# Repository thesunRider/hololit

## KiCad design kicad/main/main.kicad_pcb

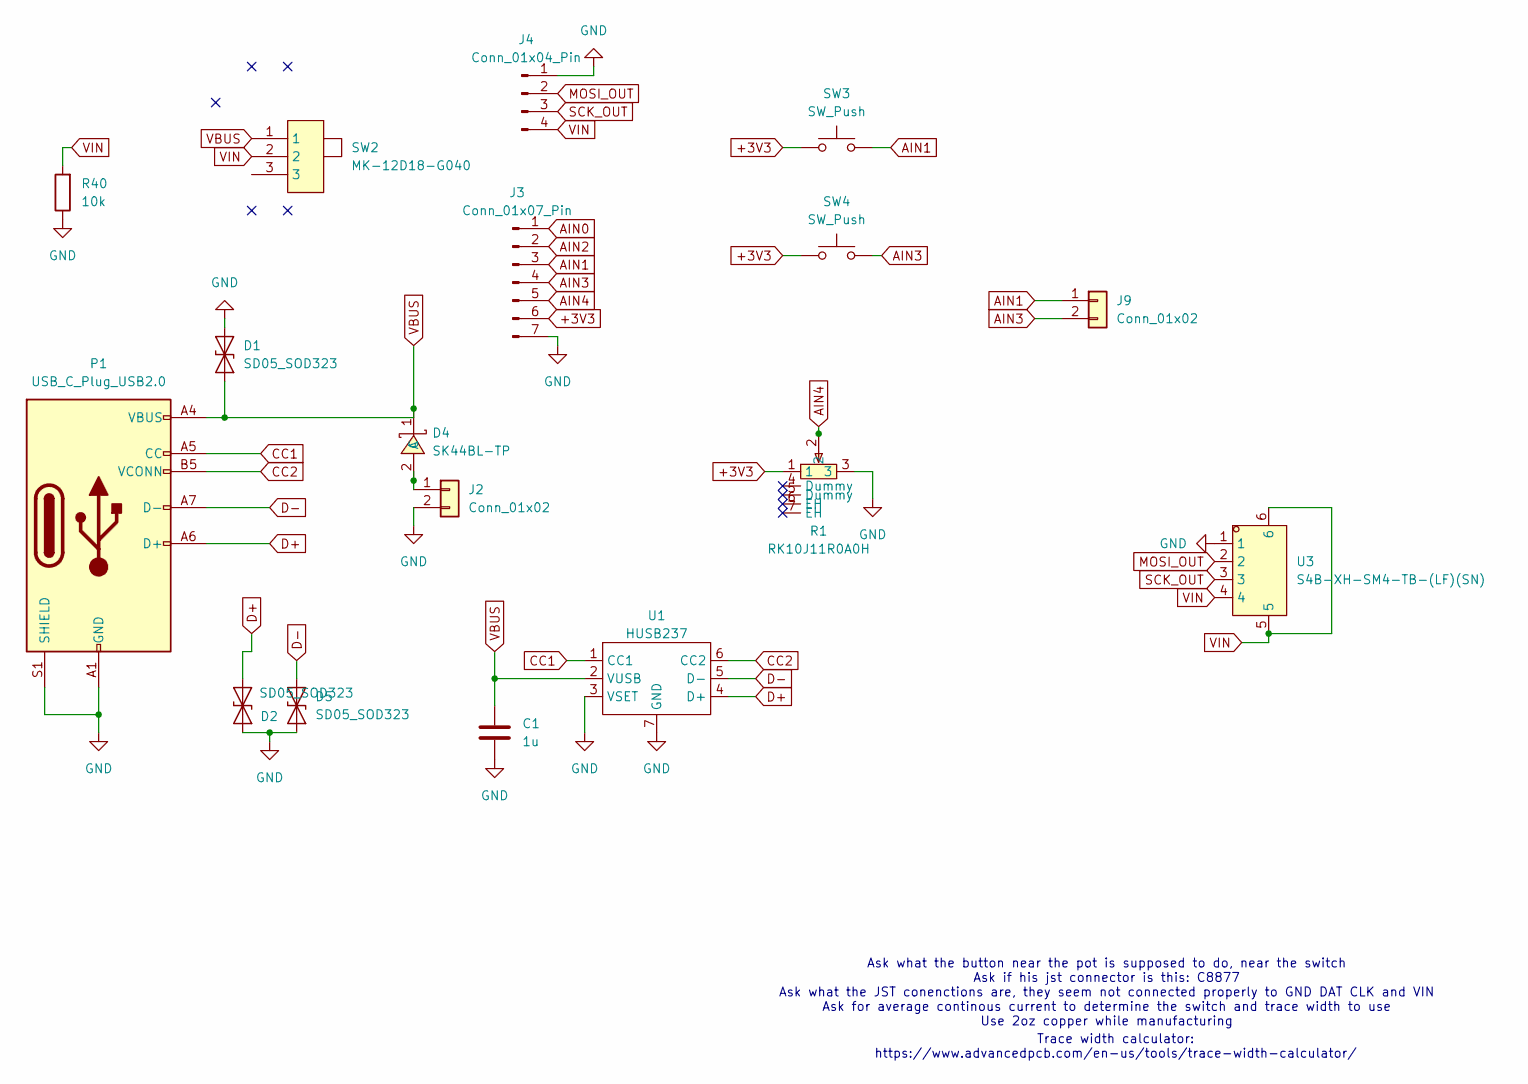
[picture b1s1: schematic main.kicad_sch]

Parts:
C1: 1u; C_0805_2012Metric
D1, D2, D5: SD05_SOD323; D_SOD-323
D4: SK44BL-TP; SMB_L4.6-W3.6-LS5.3-RD; LCSC Part C151740
J2: Conn_01x02; PinHeader_1x02_P2.54mm_Vertical
J3: Conn_01x07_Pin
J4: Conn_01x04_Pin
J9: Conn_01x02
P1: USB_C_Plug_USB2.0; USB_C_Receptacle_HRO_TYPE-C-31-M-12; Mfr Part TYPE-C-31-M-14; LCSC Part C223907
R1: RK10J11R0A0H; RES-SMD_RK10J11R0A0H; LCSC Part C470766
R40: 10k; R_0603_1608Metric_Pad0.98x0.95mm_HandSolder
SW2: MK-12D18-G040; SW-TH_MK-12D18-G040; LCSC Part C963202
SW3, SW4: SW_Push; K2-1114SA-A4SW-06; Mfr Part K2-1114SA-A4SW-06; LCSC Part C136662
U1: HUSB237; DFN-6-1EP_2x2mm_P0.65mm_EP1.01x1.7mm; LCSC Part C22373734
U3: S4B-XH-SM4-TB-(LF)(SN); CONN-SMD_S4B-XH-SM4-TB-LF-SN; LCSC Part C161861

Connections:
+3V3: J3.6, R1.1, SW3.1, SW4.1
AIN0: J3.1
AIN1: J3.3, J9.1, SW3.2
AIN2: J3.2
AIN3: J3.4, J9.2, SW4.2
AIN4: J3.5, R1.2
CC1: P1.A5 (CC), U1.1 (CC1)
CC2: P1.B5 (VCONN), U1.6 (CC2)
D+: D2.1 (A1), P1.A6 (D+), U1.4 (D+)
D-: D5.1 (A1), P1.A7 (D-), U1.5 (D-)
GND: C1.2, D1.2 (A2), D2.2 (A2), D5.2 (A2), J2.2, J3.7, J4.1, P1.A1 (GND), P1.A12 (GND), P1.B1 (GND), P1.B12 (GND), P1.S1 (SHIELD), R1.3, R40.1, U1.3 (VSET), U1.7 (GND), U3.1
MOSI_OUT: J4.2, U3.2
unnamed: D4.2 (A), J2.1
SCK_OUT: J4.3, U3.3
VBUS: C1.1, D1.1 (A1), D4.1 (C), P1.A4 (VBUS), P1.A9 (VBUS), P1.B4 (VBUS), P1.B9 (VBUS), SW2.1, U1.2 (VUSB)
VIN: J4.4, R40.2, SW2.2, U3.4, U3.5, U3.6

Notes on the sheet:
Trace width calculator: https://www.advancedpcb.com/en-us/tools/trace-width-calculator/
Ask what the button near the pot is supposed to do, near the switch Ask if his jst connector is this: C8877 Ask what the JST conenctions are, they seem not connected properly to GND DAT CLK and VIN Ask for average continous current to determine the switch and trace width to use Use 2oz copper while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

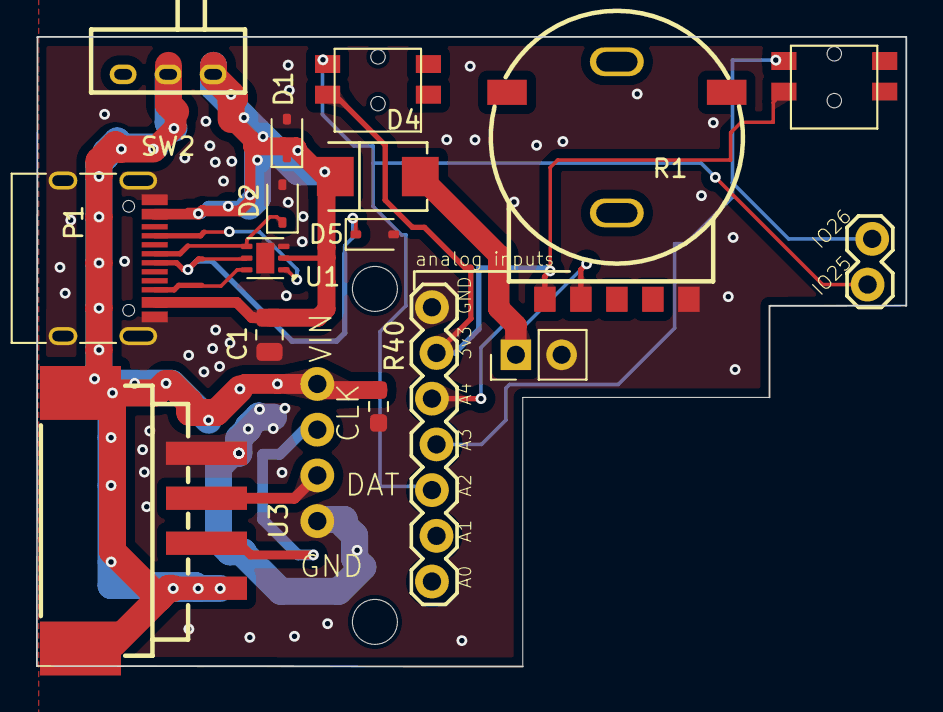
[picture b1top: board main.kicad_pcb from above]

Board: 2 copper layers, 48.3 x 35.0 mm, 19 parts (0 on the bottom side), 14 nets.

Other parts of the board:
@HOLE0, @HOLE1: (no value)

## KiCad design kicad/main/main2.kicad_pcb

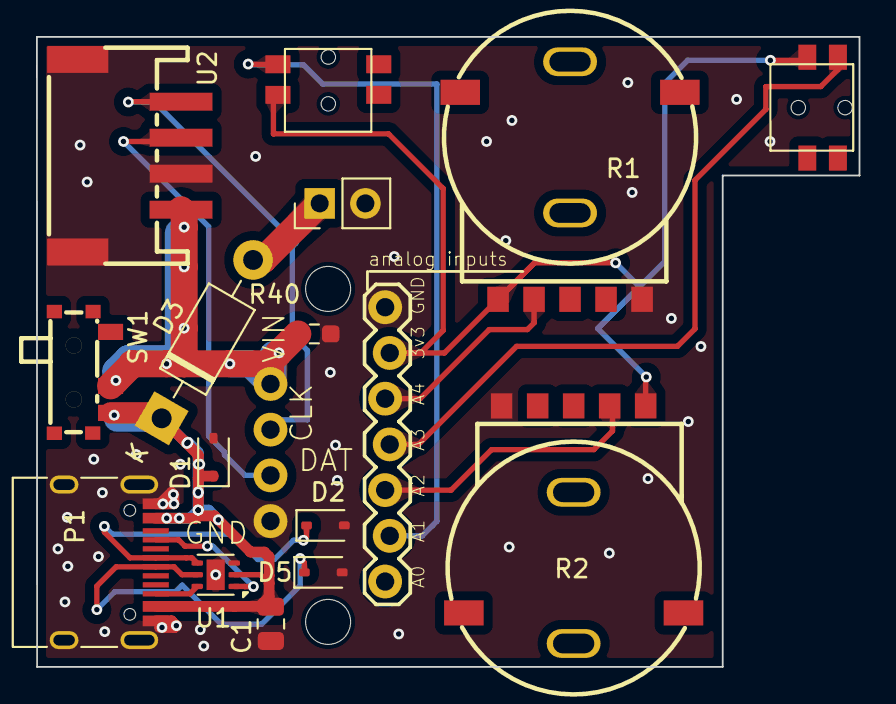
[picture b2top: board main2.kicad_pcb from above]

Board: 2 copper layers, 45.7 x 35.0 mm, 19 parts (0 on the bottom side), 15 nets.

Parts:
@HOLE0, @HOLE1: (no value)
C1: 1u; C_0805_2012Metric
D1, D2, D5: SD05_SOD323; D_SOD-323
D3: 1N4007; D_DO-41_SOD81_P10.16mm_Horizontal
J2: Conn_01x02; PinHeader_1x02_P2.54mm_Vertical
J3: Conn_01x07_Pin; 1X07_LOCK_513
J4: Conn_01x04_Pin; 1X04_NO_SILK_513
P1: USB_C_Plug_USB2.0; USB_C_Receptacle_HRO_TYPE-C-31-M-12
R1, R2: RK10J11R0A0H; RES-SMD_RK10J11R0A0H
R40: 10k; R_0603_1608Metric_Pad0.98x0.95mm_HandSolder
SW1: MK-12C03-G015; SW-SMD_MK-12C03-G015
SW3, SW4: SW_Push; K2-1114SA-A4SW-06
U1: HUSB237; DFN-6-1EP_2x2mm_P0.65mm_EP1.01x1.7mm
U2: ZX-PH2.0-WT4P; CONN-SMD_4P-P2.00_C2001RS10411M0101RC

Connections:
+3V3: J3.6, R1.1, R2.1, SW3.1, SW4.1
AIN1: J3.2, SW3.2
AIN2: J3.3, R2.2
AIN3: J3.4, SW4.2
AIN4: J3.5, R1.2
CC1: P1.A5 (CC), U1.1 (CC1)
CC2: P1.B5 (VCONN), U1.6 (CC2)
D+: D2.1 (A1), P1.A6 (D+), U1.4 (D+)
D-: D5.1 (A1), P1.A7 (D-), U1.5 (D-)
GND: C1.2, D1.2 (A2), D2.2 (A2), D5.2 (A2), J2.2, J3.7, J4.1, P1.A1 (GND), P1.A12 (GND), P1.B1 (GND), P1.B12 (GND), P1.S1 (SHIELD), R1.3, R2.3, R40.1, U1.3 (VSET), U1.7 (GND), U2.3, U2.5, U2.6
MOSI_OUT: J4.2, U2.2
unnamed: D3.2 (A), J2.1
SCK_OUT: J4.3, U2.1
VBUS: C1.1, D1.1 (A1), D3.1 (K), P1.A4 (VBUS), P1.A9 (VBUS), P1.B4 (VBUS), P1.B9 (VBUS), SW1.3, U1.2 (VUSB)
VIN: J4.4, R40.2, SW1.2, U2.4

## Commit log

2025-04-27 Added components ,2 pots 2 switches and usb
2025-04-27 Switches added
2025-04-27 Added extra switched
2025-04-27 Finished design
2025-04-27 Finished design added more vias
2025-04-27 Rotated switch
2025-04-27 Increased trace widths
2025-04-28 Added more traces
2025-04-30 added mainbase
2025-05-05 New board arrangement
2025-05-16 Rewired PCB
2025-05-16 Final push
2025-05-19 Final push with moved components
2025-07-11 Revamped PCB
